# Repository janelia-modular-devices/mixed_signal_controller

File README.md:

# mixed_signal_controller

Authors:

    Peter Polidoro <polidorop@janelia.hhmi.org>

License:

    BSD

## More Detailed Help on Installation and Usage

[modular-devices](https://github.com/janelia-modular-devices/modular-devices)

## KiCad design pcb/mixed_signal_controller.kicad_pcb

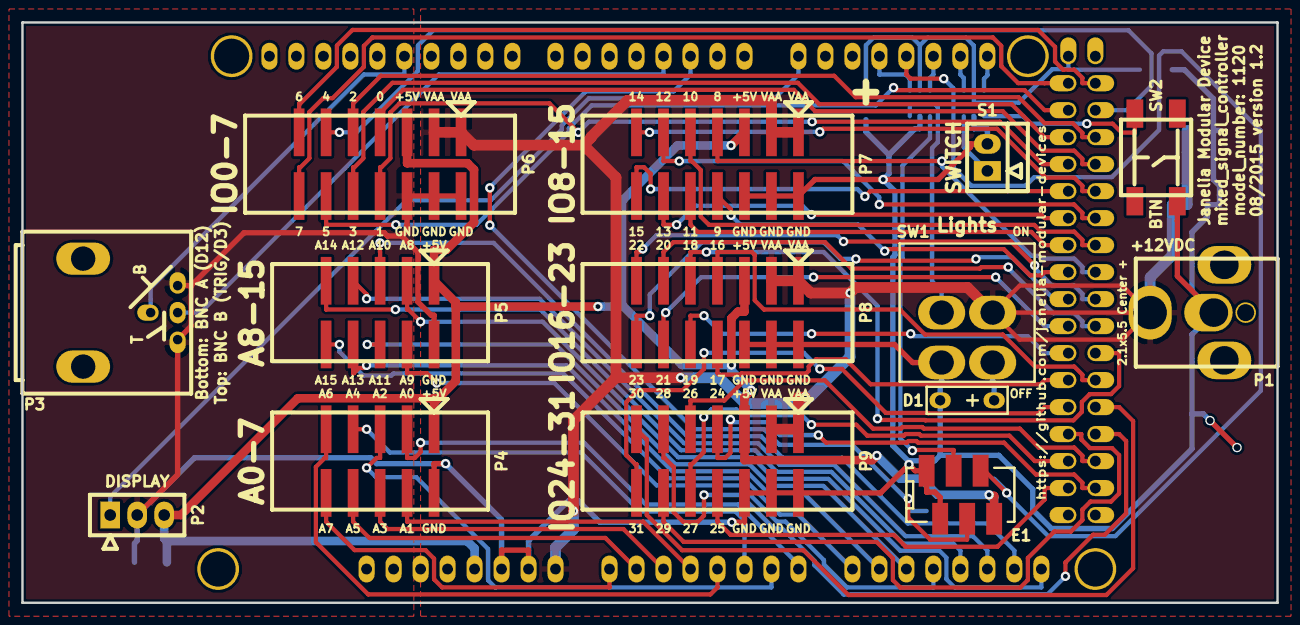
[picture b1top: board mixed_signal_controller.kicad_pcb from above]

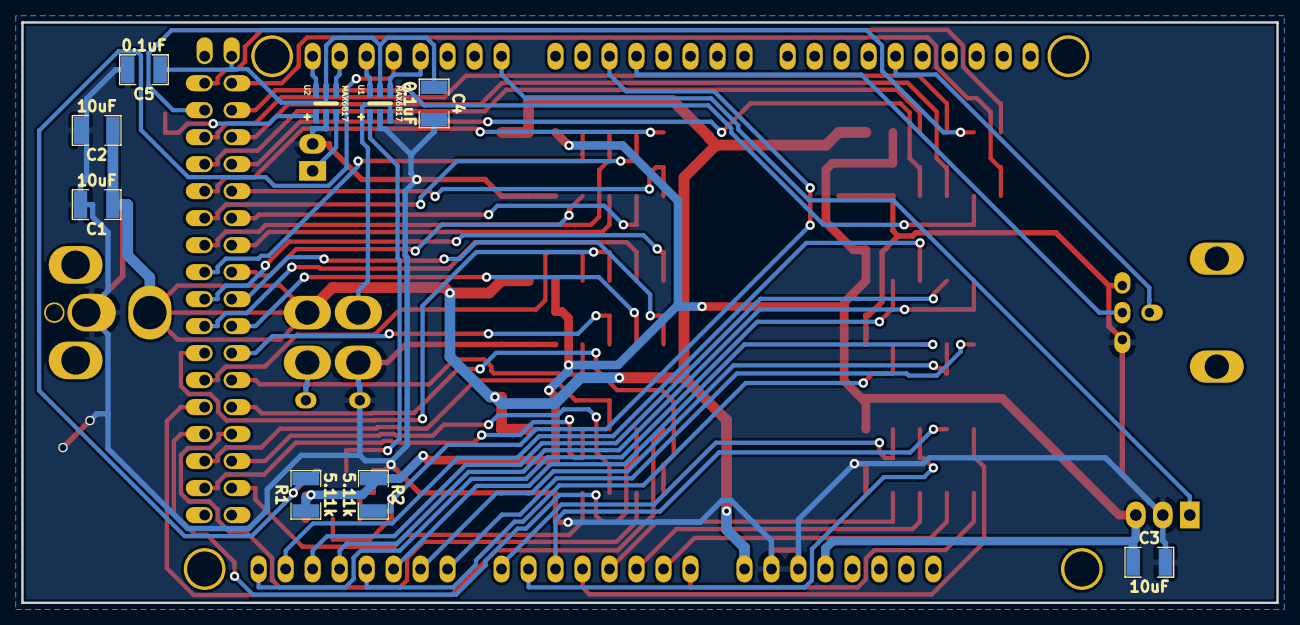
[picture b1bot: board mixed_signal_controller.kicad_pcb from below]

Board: 2 copper layers, 118.1 x 54.6 mm, 24 parts (9 on the bottom side), 66 nets.

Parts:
ARDUINO1: ARDUINO_MEGA; ARDUINO_MEGA_SHIELD
C1, C2, C3: 10uF; SM1210
C4, C5: 0.1uF; SM1210
D1: LED_24V; LED_555-3XXX
E1: ENCODER_C14; Micro-MaTch_6_SMD
P1: PWR_JACK_2.1x5.5; DCJACK_2PIN_HIGHCURRENT
P2: HEADER_01X03; Header_3_Pin
P3: BNC_DOUBLE_RA; BNC_DOUBLE
P4, P5: HEADER_02X05_SMD; HEADER_02x05_SMD
P6, P7, P8, P9: HEADER_02X07_SMD; HEADER_02x07_SMD
R1, R2: 5.11k; SM1210
S1: HEADER_01X02_SHR; Header_Shrouded_2_Pin
SW1: DPST_SERIES_M
SW2: KT_SWITCH
U1, U2: MAX6817

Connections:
+5V: ARDUINO1.5V_1, C3.1, E1.6, P2.3, P4.1, P5.1, P6.5, P7.5, P8.5, P9.5, R1.1, R2.1
+5VD: ARDUINO1.5V_4, C4.1, C5.1, U1.5, U2.5
/A0: ARDUINO1.A7, P4.3
/A1: ARDUINO1.A3, P4.4
/A2: ARDUINO1.A6, P4.5
/A3: ARDUINO1.A2, P4.6
/A4: ARDUINO1.A5, P4.7
/A5: ARDUINO1.A1, P4.8
/A6: ARDUINO1.A4, P4.9
/A7: ARDUINO1.A0, P4.10
/A8: ARDUINO1.A15, P5.3
/A9: ARDUINO1.A11, P5.4
/A10: ARDUINO1.A14, P5.5
/A11: ARDUINO1.A10, P5.6
/A12: ARDUINO1.A13, P5.7
/A13: ARDUINO1.A9, P5.8
/A14: ARDUINO1.A12, P5.9
/A15: ARDUINO1.A8, P5.10
/BNC_A: ARDUINO1.12, P3.1
/BNC_B: ARDUINO1.3, P3.3
/BTN: SW2.2, U2.1
/D_BTN: ARDUINO1.21, U2.6
/D_ENC_BTN: ARDUINO1.19, U1.6
/D_LIGHTS: ARDUINO1.17, U1.4
/D_SWITCH: ARDUINO1.20, U2.4
/ENC_A: ARDUINO1.18, E1.5, R1.2
/ENC_B: ARDUINO1.2, E1.4, R2.2
/ENC_BTN: E1.3, U1.1
/IO0: ARDUINO1.29, P6.7
/IO1: ARDUINO1.28, P6.8
/IO2: ARDUINO1.27, P6.9
/IO3: ARDUINO1.26, P6.10
/IO4: ARDUINO1.25, P6.11
/IO5: ARDUINO1.24, P6.12
/IO6: ARDUINO1.23, P6.13
/IO7: ARDUINO1.22, P6.14
/IO8: ARDUINO1.37, P7.7
/IO9: ARDUINO1.36, P7.8
/IO10: ARDUINO1.35, P7.9
/IO11: ARDUINO1.34, P7.10
/IO12: ARDUINO1.33, P7.11
/IO13: ARDUINO1.32, P7.12
/IO14: ARDUINO1.31, P7.13
/IO15: ARDUINO1.30, P7.14
/IO16: ARDUINO1.45, P8.7
/IO17: ARDUINO1.44, P8.8
/IO18: ARDUINO1.43, P8.9
/IO19: ARDUINO1.42, P8.10
/IO20: ARDUINO1.41, P8.11
/IO21: ARDUINO1.40, P8.12
/IO22: ARDUINO1.39, P8.13
/IO23: ARDUINO1.38, P8.14
/IO24: ARDUINO1.53, P9.7
/IO25: ARDUINO1.52, P9.8
/IO26: ARDUINO1.51, P9.9
/IO27: ARDUINO1.50, P9.10
/IO28: ARDUINO1.49, P9.11
/IO29: ARDUINO1.48, P9.12
/IO30: ARDUINO1.47, P9.13
/IO31: ARDUINO1.46, P9.14
/LED_PWR: D1.1, SW1.3
/LIGHTS: SW1.5, U1.3
/SWITCH: S1.1, U2.3
/TX3: ARDUINO1.14, P2.1
GND: ARDUINO1.GND1, ARDUINO1.GND2, C1.2, C2.2, C3.2, C4.2, C5.2, D1.2, E1.1, E1.2, P1.2, P2.2, P3.2, P3.4, P4.2, P5.2, P6.2, P6.4, P6.6, P7.2, P7.4, P7.6, P8.2, P8.4, P8.6, P9.2, P9.4, P9.6, S1.2, SW1.6, SW2.3, U1.2, U2.2
VAA: ARDUINO1.V_IN, C1.1, C2.1, P1.1, P6.1, P6.3, P7.1, P7.3, P8.1, P8.3, P9.1, P9.3, SW1.2

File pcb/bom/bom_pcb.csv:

Item,Reference(s),Value,Quantity,Description,PartNumber,Vendor
1,ARDUINO1,ARDUINO_MEGA,1,BOARD MCU MEGA2560,1050-1018-ND,digikey
2,C1 C2 C3,10uF,3,CAP CER 10UF 50V 10% X7S 1210,445-4536-1-ND,digikey
3,C4 C5,0.1uF,2,CAP CER 0.1UF 50V 10% X7R 1210,478-3586-1-ND,digikey
4,D1,LED_24V,1,LED 2MM 24V VERTICAL RED PC MNT,350-1723-ND,digikey
5,E1,ENCODER_C14,1,CONN FMALE-ON-BRD 6POS VERT SMD,A99474CT-ND,digikey
6,P1,PWR_JACK_2.1x5.5,1,CONN PWR JACK DC 2.1X5.5 8A T/H,CP-063AH-ND,digikey
7,P2,HEADER_01X03,1,01x03 .100 SR STRAIGHT,609-3461-ND,digikey
8,P3,BNC_DOUBLE_RA,1,CONN BNC JACK R/A 75 OHM PCB,ACX1655-ND,digikey
9,P4 P5,HEADER_02X05_SMD,2,CONN_HEADR_2.54MM_10POS_GOLD_SMD,S9185-ND,digikey
10,P6 P7 P8 P9,HEADER_02X07_SMD,4,CONN HEADR 2.54MM 14POS GOLD SMD,S9186-ND,digikey
11,R1 R2 R3,5.11k,3,RES SMD 5.11K OHM 1% 1/2W 1210,P5.11KAACT-ND,digikey
12,S1,HEADER_01X02_SHR,1,CONN HEADER 2POS .100 VERT GOLD,WM4800-ND,digikey
13,SW1,SPST_SERIES_M,1,SWITCH TOGGLE SPST 6A 125V,360-3243-ND,digikey
14,SW2,KT_SWITCH,1,SWITCH TACTILE SPST-NO 1VA 32V,CKN1860CT-ND,digikey
15,U1 U2,MAX6817,2,IC DEBOUNCER SWITCH DUAL SOT23-6,MAX6817EUT+TCT-ND,digikey

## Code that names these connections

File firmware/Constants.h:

// ----------------------------------------------------------------------------
// Constants.h
//
//
// Authors:
// Peter Polidoro peter@polidoro.io
// ----------------------------------------------------------------------------
#ifndef CONSTANTS_H
#define CONSTANTS_H
#include "ConstantVariable.h"

namespace constants
{
//MAX values must be >= 1, >= created/copied count, < RAM limit
enum{SAVED_VARIABLE_COUNT_MAX=1};
enum{PARAMETER_COUNT_MAX=5};
enum{METHOD_COUNT_MAX=26};

enum{DISPLAY_LABEL_COUNT_MAX=22};
enum{DISPLAY_VARIABLE_COUNT_MAX=20};
enum{INTERACTIVE_VARIABLE_COUNT_MAX=2};
enum {FRAME_COUNT=7};

enum {AIN_COUNT=16};
enum {CHANNEL_COUNT=32};
enum {STATE_COUNT=16};
enum {CHANNELS_DISPLAY_COUNT=4};
enum {INDEXED_SET_UNTILS_COUNT_MAX=1};
enum {FILTER_SAMPLE_COUNT=5};
enum {INDEXED_SET_FORS_COUNT_MAX=8};

extern const unsigned int baudrate;

extern const unsigned int model_number;

extern const unsigned char firmware_major;
extern const unsigned char firmware_minor;
extern const unsigned char firmware_patch;

extern HardwareSerial & display_serial;

extern const int enc_a_pin;
extern const int enc_b_pin;
extern const int enc_btn_pin;
extern const int enc_btn_int;
extern const int btn_pin;
extern const int btn_int;
extern const int lights_pin;
extern const int standalone_update_period;

extern const int ain_pins[AIN_COUNT];

extern const int ain_min;
extern const int ain_max;

extern const int percent_min;
extern const int percent_max;

extern const int ain_value_min;
extern const int ain_value_max;

extern const int set_until_update_period;

extern const int duration_min;
extern const int duration_max;

extern const uint8_t filter_block_ain_count;
extern const uint8_t filter_update_period;
extern const boolean use_filters;

extern const uint8_t ain_dsp_lbl_display_positions[AIN_COUNT];

extern const uint8_t ain_dsp_lbl_width;
extern const uint8_t percent_display_width;

extern const uint8_t ain_dsp_var_display_positions[AIN_COUNT];

extern const int io_pins[CHANNEL_COUNT];

extern const uint32_t states_array_default[STATE_COUNT];

extern const uint8_t channel_dsp_lbl_display_position;
extern const uint8_t channel_int_var_display_position;
extern const uint8_t channels_dsp_lbl_display_positions[CHANNELS_DISPLAY_COUNT];
extern const uint8_t channels_dsp_var_display_positions[CHANNELS_DISPLAY_COUNT];
extern const uint8_t channels_dsp_var_display_width;

extern const uint8_t state_dsp_lbl_display_position;
extern const uint8_t state_int_var_display_position;

extern ConstantString duration_units;

extern ConstantString states_name;

extern ConstantString channel_dsp_lbl_str;

extern ConstantString device_name;

extern ConstantString ain_parameter_name;
extern ConstantString channels_parameter_name;
extern ConstantString state_parameter_name;
extern ConstantString duration_parameter_name;
extern ConstantString ain_value_parameter_name;

extern ConstantString execute_standalone_callback_method_name;
extern ConstantString get_leds_powered_method_name;
extern ConstantString get_analog_inputs_method_name;
extern ConstantString get_analog_inputs_filtered_method_name;

extern ConstantString set_channels_on_method_name;
extern ConstantString set_channels_off_method_name;
extern ConstantString toggle_channels_method_name;
extern ConstantString toggle_all_channels_method_name;
extern ConstantString set_all_channels_on_method_name;
extern ConstantString set_all_channels_off_method_name;
extern ConstantString set_channels_on_all_others_off_method_name;
extern ConstantString set_channels_off_all_others_on_method_name;
extern ConstantString get_channels_on_method_name;
extern ConstantString get_channels_off_method_name;
extern ConstantString get_channel_count_method_name;

extern ConstantString save_state_method_name;
extern ConstantString recall_state_method_name;
extern ConstantString get_saved_states_method_name;

extern ConstantString set_channels_on_until_method_name;
extern ConstantString set_channels_off_until_method_name;
extern ConstantString are_all_set_untils_complete_method_name;
extern ConstantString remove_all_set_untils_method_name;

extern ConstantString set_channels_on_for_method_name;
extern ConstantString set_channels_off_for_method_name;
extern ConstantString are_all_set_fors_complete_method_name;
extern ConstantString remove_all_set_fors_method_name;

extern ConstantString frame0_name;
extern ConstantString frame1_name;
extern ConstantString frame2_name;
extern ConstantString frame5_name;
extern const ConstantString frame_name_array[FRAME_COUNT];

extern ConstantString ain0_dsp_lbl_str;
extern ConstantString ain1_dsp_lbl_str;
extern ConstantString ain2_dsp_lbl_str;
extern ConstantString ain3_dsp_lbl_str;
extern ConstantString ain4_dsp_lbl_str;
extern ConstantString ain5_dsp_lbl_str;
extern ConstantString ain6_dsp_lbl_str;
extern ConstantString ain7_dsp_lbl_str;
extern ConstantString ain8_dsp_lbl_str;
extern ConstantString ain9_dsp_lbl_str;
extern ConstantString ain10_dsp_lbl_str;
extern ConstantString ain11_dsp_lbl_str;
extern ConstantString ain12_dsp_lbl_str;
extern ConstantString ain13_dsp_lbl_str;
extern ConstantString ain14_dsp_lbl_str;
extern ConstantString ain15_dsp_lbl_str;
extern const ConstantString ain_dsp_lbl_strs[AIN_COUNT];
extern ConstantString channels0_dsp_lbl_str;
extern ConstantString channels1_dsp_lbl_str;
extern ConstantString channels2_dsp_lbl_str;
extern ConstantString channels3_dsp_lbl_str;
extern const ConstantString channels_dsp_lbl_strs[CHANNELS_DISPLAY_COUNT];
}
#endif

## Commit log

2015-05-01 Initial commit of base files.
2015-05-01 Finished pcb v1.0.
2015-05-01 Initial bom commit.
2015-05-05 Updated bom_pcb_add.
2015-05-05 Finished firmware version 1.0.
2015-05-08 Finished pcb v1.1.
2015-05-12 Changed order quantities.
2015-05-12 Added 12V power supply to bom.
2015-05-18 Added methods.
2015-05-19 Increased AIN_COUNT from 8 to 16.
2015-05-20 Added set of digital io methods.
2015-05-22 Added standalone_interface frame toggleChannel.
2015-05-22 Added states methods.
2015-05-22 Added standalone frames setAllChannelsOn and setAllChannelsOff.
2015-05-26 Added channels display variables.
2015-05-27 Partial update towards setUntil methods.
2015-05-29 Added more setUntil methods.
2015-05-29 Updated documentation.
2015-06-18 Average the analog input over several samples.
2015-06-23 Use new analogSampled function instead of simple analogRead.
2015-07-02 Increasing analog sample count creates serial response errors.
2015-07-13 JaneliaSciComp -> janelia-modular-devices.
2015-07-23 Use ain_value instead of percent for feedback.
2015-07-24 Updated author/license.
2015-07-24 Moved README info.
2015-07-28 boolean -> bool.
2015-08-03 Removed all analog min/max functions to free up resources.
2015-08-04 Added filtering to the analog inputs.
2015-08-05 Added setFor methods.
2015-08-11 SPST switch -> DPST switch.
2015-09-18 Updated firmware to match pcb v1.2.
2015-10-15 Added GenericSerial.
2015-10-16 Updated first header.
2015-12-08 Updated to match upgrades in ModularDevice library.
2015-12-11 ModularDevice -> ModularServer.
2015-12-11 ModularStandalone -> StandaloneInterface.
2016-01-08 Updated from arrays to vectors.
2016-01-08 Changed order of methods, parameters, and saved_variables.
2016-09-19 Updated spaces around pointers and references.
2016-09-21 pcb -> hardware.
2018-04-12 *.md -> *.org.
2018-08-12 polidorop@janelia.hhmi.org -> peterpolidoro@gmail.com
2018-08-27 Combined software and hardware licenses.
2021-09-17 Update email address
